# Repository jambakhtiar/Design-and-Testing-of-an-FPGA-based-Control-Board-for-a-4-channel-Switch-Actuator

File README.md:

Abstract
This project work consists of two sub-projects. On the one hand, a control board for a 4-channel
switch actuator was to be newly designed. The switch actuator has four relays that can be freely
controlled. In addition to the four buttons built into the housing, the new control board should allow
control via RS485 bus. In previous project works, this had already been carried out, but for this
work, an FPGA was to be used for the first time.
The FPGA used is a MachXO2-1200 from Lattice and is on a TinyFPGA AX2 development board.
The development board is so small that it can easily be mounted on the designed board via pin
headers.
In the second part of the work, a predefined communication protocol and all necessary
functionalities, as well as the control of the four buttons, are to be implemented on the FPGA. The
hardware description of the FPGA was done in the description language VHDL and is transferred to
the FPGA via a programmer. A MicroMatch interface should be placed on the control board for the
programmer.
Table of Contents
Statutory Declaration i
Abstract ii
Table of Contents iiiList of Figures vi
List of Tables vii
List of Abbreviations viii
1. Introduction 1
1.1. Objective of the Work 1
1.2. Procedure 1
2. Fundamentals 2
2.1. Data Exchange 2
2.2. Debouncing the Buttons 3
3. Problem Analysis 4
3.1. Communication Protocol 5
3.1.1. Message Fragments 6
3.1.2. Commands 6
3.1.3. Error Messages 7
4. Solution Concept 8
4.1. Reading Serial Data 8
4.2. Assembling Data 8
4.3. Generating CRC Checksum 9
4.4. Evaluating Commands 9
4.4.1. Executing Commands 9
4.5. Sending Message 10
4.5.1. Generating a Response 10
4.5.2. Sending Serial Data 10
4.6. Top Module 11
5. Implementation 12
5.1. The Module serial_reciever 12
5.1.1. Idle 13
5.1.2. Start 13
5.1.3. Data 14
5.1.4. Stop 14
5.2. The Module msg_separator 15
5.2.1. Reset 165.2.2. States 16
5.3. The Module crc_generator 17
5.4. The Module state_logic 17
5.4.1. Button Control 18
5.4.2. The Module msg_interpreter 19
5.5. The Module sender_modul 20
5.5.1. The Module msg_composer 21
5.5.2. The Module serial_sender 22
5.6. The Clock Generator 24
5.7. The Top Module 24
5.7.1. Startup and Idle 25
5.7.2. Receive and Check_crc 26
5.7.3. Check_addr 27
5.7.4. Check_cmd and exec_cmd 27
5.7.5. Send 28
5.7.6. Error States 28
6. Board Design 29
7. Commissioning 32
8. Evaluation 34
9. Summary and Outlook 35
Literature 36
A. Source Code 37
B. Circuit Diagram 42
List of Figures
5.1. Pin Assignments of the FPGA 25
6.1. FPGA with MAX485 29
6.2. Extended Board Design 30
6.3. Copper Layer has no contact to the outside on both sides 31
7.1. Buttons 1-4 and on the far left Reset; LEDs 1-4 in the back 32
List of Tables3.1. Division of Messages 6
3.2. Overview of which Relays are associated with which Operands 7
3.3. Overview of the Defined Error Codes 7
List of Abbreviations
ASCII: American Standard Code for Information Interchange 5
CR: Carriage Return 5
CRC: Cyclic Redundancy Check 4
FPGA: Field Programmable Gate Array 1
IDE: Integrated Development Environment 25
LED: Light Emitting Diode 1
LSB: Least Significant Bit 2
UART: Universal Asynchronous Receiver Transmitter 2
VHDL: Very High Speed Integrated Circuit Hardware Description Language 1
1. Introduction
During the Bachelor's degree program in Computer Science, a project with 150 hours of work is to
be completed. Due to previous collaboration with Prof. Dr. Rainer Werthebach, the idea arose to
reimplement an older project with different hardware. This involves an ELV switching module,
whose control board is to be replaced with a variant that is operated by an FPGA (Field
Programmable Gate Array).
1.1. Objective of the Work
The main objectives of this work are the design of a control board and the description of an FPGA
located on it, which allows control via the RS485 bus.
1.2. Procedure
Initially, there was a phase of familiarization with the VHDL (Very High-Speed Integrated Circuit
Hardware Description Language) description of the FPGA using the Lattice toolchain. This was
done through small test projects where LEDs (Light Emitting Diodes) and buttons were used.
Subsequently, the functionalities to be implemented were divided into individual modules, which
were then implemented and tested one by one.
Since hardware description, unlike usual programming, does not function sequentially, an
adjustment was necessary. The use of state machines proved beneficial in this regard. As they are
also very helpful for the conceptualization of processes, they were used more frequently.In parallel, there was a familiarization with circuit diagram and PCB design using the KiCad
software version 5.1.6. Based on previous project works, the control board was designed.
2. Fundamentals
2.1 Data Exchange
While the input and output signals of the control board take place via an RS485 interface, the
signals generated from it are subject to a UART (Universal Asynchronous Receiver Transmitter)
interface. This is an asynchronous, serial interface that is implemented without a clock signal. For
this work, a baud rate of 9600 bit/s is used. Since UART only allows simplex transmission, both a
sending and a receiving line are necessary.
The lines are continuously at a logical one until a logical zero arrives with the start bit of the
message stream. The following eight bits are the data bits of the message, starting with the LSB
(Least Significant Bit), followed by a logical one as the stop bit. Thus, data is transmitted byte by
byte.
Since custom modules are to be written in VHDL for serial transmission, it is necessary to measure
the bits correctly. If the value of a bit is measured immediately at the falling or rising edge of a
signal, reading the data is prone to errors. If the signal does not change its state quickly enough, it
could not be read reliably.
To avoid this source of error, one must wait until the middle of the bit after the edge has fallen and
only then measure. This ensures that the signal is at its desired HIGH or LOW voltage.
For the receiver module, one needs the number of clock cycles between the individual bits and must
start reading the data bits after half of this number. The number is calculated from the clock
frequency and the baud rate. The clock generator is built into the FPGA and is used with a
frequency of 2.08 MHz. This results in the following calculation:
Takte_pro_Bit=BaudrateTaktfrequenz
Takte_pro_Bit=9,6002,080,000≈216.667
Thus, the signal of a bit must be maintained for 217 cycles.
This value must also be used for sending the data to set the signals at the correct intervals to achieve
a baud rate of 9600.
2.2. Debouncing the Buttons
For the use of buttons, the interference effect of bouncing must be considered. This occurs due to
the mechanical pressing, where the contacts briefly spring back before making the final contact. As
a result, a stable signal is only present after a short time, and the state is fluctuating before that.
Depending on the function of the button, bouncing can lead to unwanted effects.
There are various ways to debounce buttons. In this case, debouncing is done in the FPGA using
VHDL. Upon detecting a signal, it is measured after 50 ms to see if the signal is still present, and
only then is the desired function executed. This time period is hardly noticeable for the user and issufficient to bridge the bouncing, as the bouncing times can reach up to 10 ms depending on the
button.
For this, the necessary number of clock cycles must also be calculated.
time cycles per msWait time=Clock cycles per ms×50
2080×50=104000
Section 3: Problem Analysis
The switch actuator is controlled by four signals originating from the control board. This results in
16 different states of the relays. To visualize this, four LEDs are located on the top side of the
casing to display the current state of each relay.
Additionally, the states should be toggleable manually using the buttons also located on the top side
of the casing.
The board should have an RS485 interface, which converts RS485 signals into serial signals and
forwards them to the FPGA. It should also have the same dimensions as the original board, a
voltage converter for power supply, a reset button, and a MicroMatch interface for the TinyFPGA
Programmer.
For serial signals, implementing read and write modules is necessary. Transmitted bytes must be
linked into a coherent message to check the message length. Subsequently, the message syntax must
be correct, and the proper CRC1 checksum must be calculated. If the addresses and the command
match, the command will be executed.
The FPGA requires the following inputs and outputs for these functionalities:
•
•
•
•
•
•
•
•
•
•
•
•
reset: Input
button0: Input
button1: Input
button2: Input
button3: Input
relay0: Output
relay1: Output
relay2: Output
relay3: Output
serial_in: Input
serial_out: Output
serial_enable: Output
3.1 Communication Protocol
Communication and control should take place serially over an RS485 bus. ASCII-coded bytes are
sent to make them readable in a terminal. An existing protocol from previous projects defines the
commands. The protocol specifications are:
• Message length: 12 bytes
• Encoding in ASCII•
•
•
•
•
•
Messages end with CR3
Baud rate: 9600
One start bit
Eight data bits, LSB first
One stop bit
No parity bit
3.1.1 Message Fragments
The message fragments are structured as follows:
Fragment
Encoding
Length Example
Receiver
Four numerical values, ASCII-coded 4 bytes 1001
Sender
Four numerical values, ASCII-coded 4 bytes 1001
Message
Operator + Operand, ASCII-coded 3 bytes s01
CRC Checksum
ASCII characters
4 bytes AB01
CR - Carriage Return ASCII character: CR (0x0D)
1 byte
Table 3.1: Structure of the messages
3.1.2 Commands
There are five different commands:
•
•
•
•
•
s: Turns the relay on
c: Turns the relay off
t: Toggles the relay
g: Queries the state of all relays
d: Performs a self-test (not yet defined)
3.1.3 Error Messages
Errors should be detected and reported back. Various error codes are defined for reporting, listed in
Table 3.3.
Error Code
Description
E01
CRC checksum incorrect
E02
Unknown error
E03
Packet length incorrect
E04
Command does not match the specified syntax
E05
Sender is not authorized to issue commands
Table 3.3: Overview of the defined error codes
Section 4: Solution Concept
Most functionalities can be divided into individual modules. In almost all cases, it has proven useful
to first design state machines. These allow sequential structures to be easily implemented in VHDL.4.1. Reading Serial Data
The work of the module for serial reception was based on a template. [2] From this, the necessary
processes were determined and also code parts for later implementation were taken.
A UART frame consists of ten bits. The first is the start bit, followed by eight data bits and finally
the stop bit. The data bits can be combined into a byte. Thus, it must first wait until a start bit is
detected. Then, the data bit is read eight times with the delay calculated in 2.1 and combined into a
byte. After the stop bit, the module signals that a new byte has been read.
4.2. Assembling Data
To process the data, the individual bytes must first be combined into the components of the message
protocol.
4.3. Generating CRC Checksum
Next, the syntax of the message must be correct, and the correct CRC1 checksum must be
calculated. If the addresses and the command match, the command is executed.
The FPGA requires the following inputs and outputs for these functionalities:
•
•
•
•
•
•
•
•
•
•
•
•
reset: input
taster0: input
taster1: input
taster2: input
taster3: input
relais0: output
relais1: output
relais2: output
relais3: output
serial_in: input
serial_out: output
serial_enable: output
4.4. Evaluating Commands
Commands are interpreted and executed based on predefined protocols and syntax.
4.5. Sending Messages
This involves generating a response and transmitting it serially.
4.6. Top Module
Combines all the submodules into a cohesive system .Section 5: Implementation
5.1 The Module serial_receiver
The serial_receiver module handles the reception of serial data. It consists of several states
that manage the reception process:
•
•
•
•
Idle: The module waits for a start bit.
Start: The start bit is detected and validated.
Data: Data bits are received.
Stop: The stop bit is validated and the complete byte is transferred.
vhdl
Copy code
entity SERIAL_RECEIVER is
port (
clk : in std_logic;
reset : in std_logic;
rx : in std_logic;
data_out : out std_logic_vector(7 downto 0);
ready : out std_logic
);
end SERIAL_RECEIVER;
5.2 The Module msg_separator
The msg_separator module is responsible for splitting incoming messages into their respective
components. This includes resetting the module, handling various states, and signaling errors.
5.2.1 Reset
The reset functionality clears all internal counters and sets the state machine back to its initial state.
vhdl
Copy code
if in_reset = '1' then
out_e3_signal <= '0';
counter_rec <= 0;
counter_snd <= 0;
counter_cmd <= 0;
counter_crc <= 0;
msg_receiver <= (others => '0');
msg_sender <= (others => '0');
msg_cmd <= (others => '0');
msg_crc <= (others => '0');
fsm_state <= receiver;
end if;
5.2.2 States
The module transitions through several states to separate the message components.
vhdl
Copy code
elsif in_signal = '1' then
case fsm_state is
when receiver =>
if in_msg = cr_ref thenfsm_state <= receiver;
counter_rec <= 0;
out_e3_signal <= '1';
else
<= in_msg;
msg_receiver(7 + (counter_rec * 8) downto 0 + (counter_rec * 8))
if counter_rec < 3 then
counter_rec <= counter_rec + 1;
else
fsm_state <= sender;
counter_rec <= 0;
end if;
end if;
when sender =>
-- Additional state logic
when cmd =>
-- Additional state logic
when crc =>
-- Additional state logic
when cr =>
if in_msg = cr_ref then
msg_cr <= in_msg;
msg_done <= '1';
fsm_state <= receiver;
else
out_e3_signal <= '1';
fsm_state <= receiver;
end if;
end case;
end if;
5.3 The Module crc_generator
The crc_generator module calculates the CRC checksum for the received message.
vhdl
Copy code
entity CRC_GENERATOR is
port (
clk : in std_logic;
in_signal : in std_logic;
in_rec : in std_logic_vector(31 downto 0);
in_sender : in std_logic_vector(31 downto 0);
in_cmd : in std_logic_vector(23 downto 0);
out_signal : out std_logic;
out_crc : out std_logic_vector(31 downto 0)
);
end CRC_GENERATOR;
5.4 The Module state_logic
The state_logic module manages state transitions and the execution of commands.
vhdl
Copy code
entity STATE_LOGIC is
port (
clk : in std_logic;
reset : in std_logic;
msg_signal : in std_logic;
button_signal : in std_logic;
in_cmd : in std_logic_vector(23 downto 0);in_button0 : in std_logic;
in_button1 : in std_logic;
in_button2 : in std_logic;
in_button3 : in std_logic;
state_out : out std_logic_vector(3 downto 0);
state_msg : out std_logic_vector(23 downto 0);
request_signal : out std_logic;
out_e2_signal : out std_logic;
out_e4_signal : out std_logic
);
end STATE_LOGIC;
5.4.1 Button Operation
When a button is pressed during the idle state, the state machine transitions to btn_proc to
process the button press.
vhdl
Copy code
when btn_proc =>
v_Count := v_Count + 1;
if v_Count = 104000 then
if button_signal = '1' then
if in_button0 = '0' then
current_state(0) <= not current_state(0);
end if;
if in_button1 = '0' then
current_state(1) <= not current_state(1);
end if;
if in_button2 = '0' then
current_state(2) <= not current_state(2);
end if;
if in_button3 = '0' then
current_state(3) <= not current_state(3);
end if;
fsm_lgc_state <= fin;
else
v_Count := 0;
fsm_lgc_state <= idle;
end if;
end if;
5.5 The Module sender_modul
The sender_modul handles the sending of messages, including composing the message and
transmitting it via serial communication.
5.5.1 The Module msg_composer
This module assembles the message to be sent.
5.5.2 The Module serial_sender
The serial_sender transmits the composed message over the serial interface.Section 6: PCB Design
During the project, the FPGA was only used in a test setup on breadboards.
Figure 6.1: FPGA with MAX485
However, a carrier board should be designed on which the tinyFPGA board can be mounted.
Additionally, a reset button and a MicroMatch port for programming the FPGA should be added.
For the design, power supply, RS485 interface, and dimensions from a previous project were
adopted. Expanding this was a task of lesser size.
Initially, the circuit diagram was designed, with some elements also taken from the previous work
(see Appendix B).
Figure 6.2: Extended PCB Design
When routing the traces, it must be ensured that they do not run at 90-degree angles, do not cross
each other, and are not too close together. The angles can usually be maintained with the automation
provided by KiCad, although manual correction is sometimes necessary. In case of space issues, it is
helpful to narrow the traces in places or move them to the other side of the board.
Section 7: Commissioning
For commissioning, the button/LED board was replicated on a breadboard with an additional reset
button. This setup allowed for testing whether the outputs were correctly switched and the buttons
were properly read at any time. This was particularly useful during the development phase for basic
debugging.
Figure 7.1: Buttons 1-4 and reset on the far left; LEDs 1-4 at the back
At the end, it was checked whether the actual board worked the same way with the FPGA. Since
wiring errors could have occurred during the reconstruction, this was a necessary step. It turned out
that the circuit diagram was correctly read and implemented.
The control via terminal was successfully tested. All commands are executed correctly, and in case
of errors, the corresponding error messages are returned. Only the generation of the CRC checksum
remains an unresolved problem. The development of the CRC module was mainly carried out using
the simulator to be able to trace the calculated values step by step. While the checksums were
correctly displayed in the simulator, they were always the same and therefore incorrect during
actual operation. It was not possible to determine what caused this problem.
Since the control board was only designed but not created at the time of the project, actual
commissioning was not yet possible.
It also turned out that the programmer, which is plugged into the tinyFPGA board, has an impact on
the MAX485 module. Therefore, the serial ports cannot be used without the programmer attached.
Since the programmer was attached the entire time during the development phase, this was only
noticed at the very end.Section 8: Evaluation
The fundamental tasks were successfully completed. Relays can be toggled with debounced buttons,
commands transmitted via RS485 are correctly processed, and executed according to the
communication protocol. Errors mentioned there are also detected and acknowledged with
corresponding messages.
A new control board was designed to accommodate the tinyFPGA board, featuring a MicroMatch
port and the necessary components for power supply and RS485 interface. The dimensions of the
original board were maintained to allow installation in the ELV switch actuator housing.
Section 9: Summary and Outlook
The description of the FPGA makes it possible to control the relays of an ELV switch actuator via
an RS485 bus. Control can also be achieved by pressing the built-in buttons. It is possible to control
multiple devices differently, provided they are connected via the same bus.
With the developed interface, these switch actuators can automate further actuators. Potential
applications include home automation.

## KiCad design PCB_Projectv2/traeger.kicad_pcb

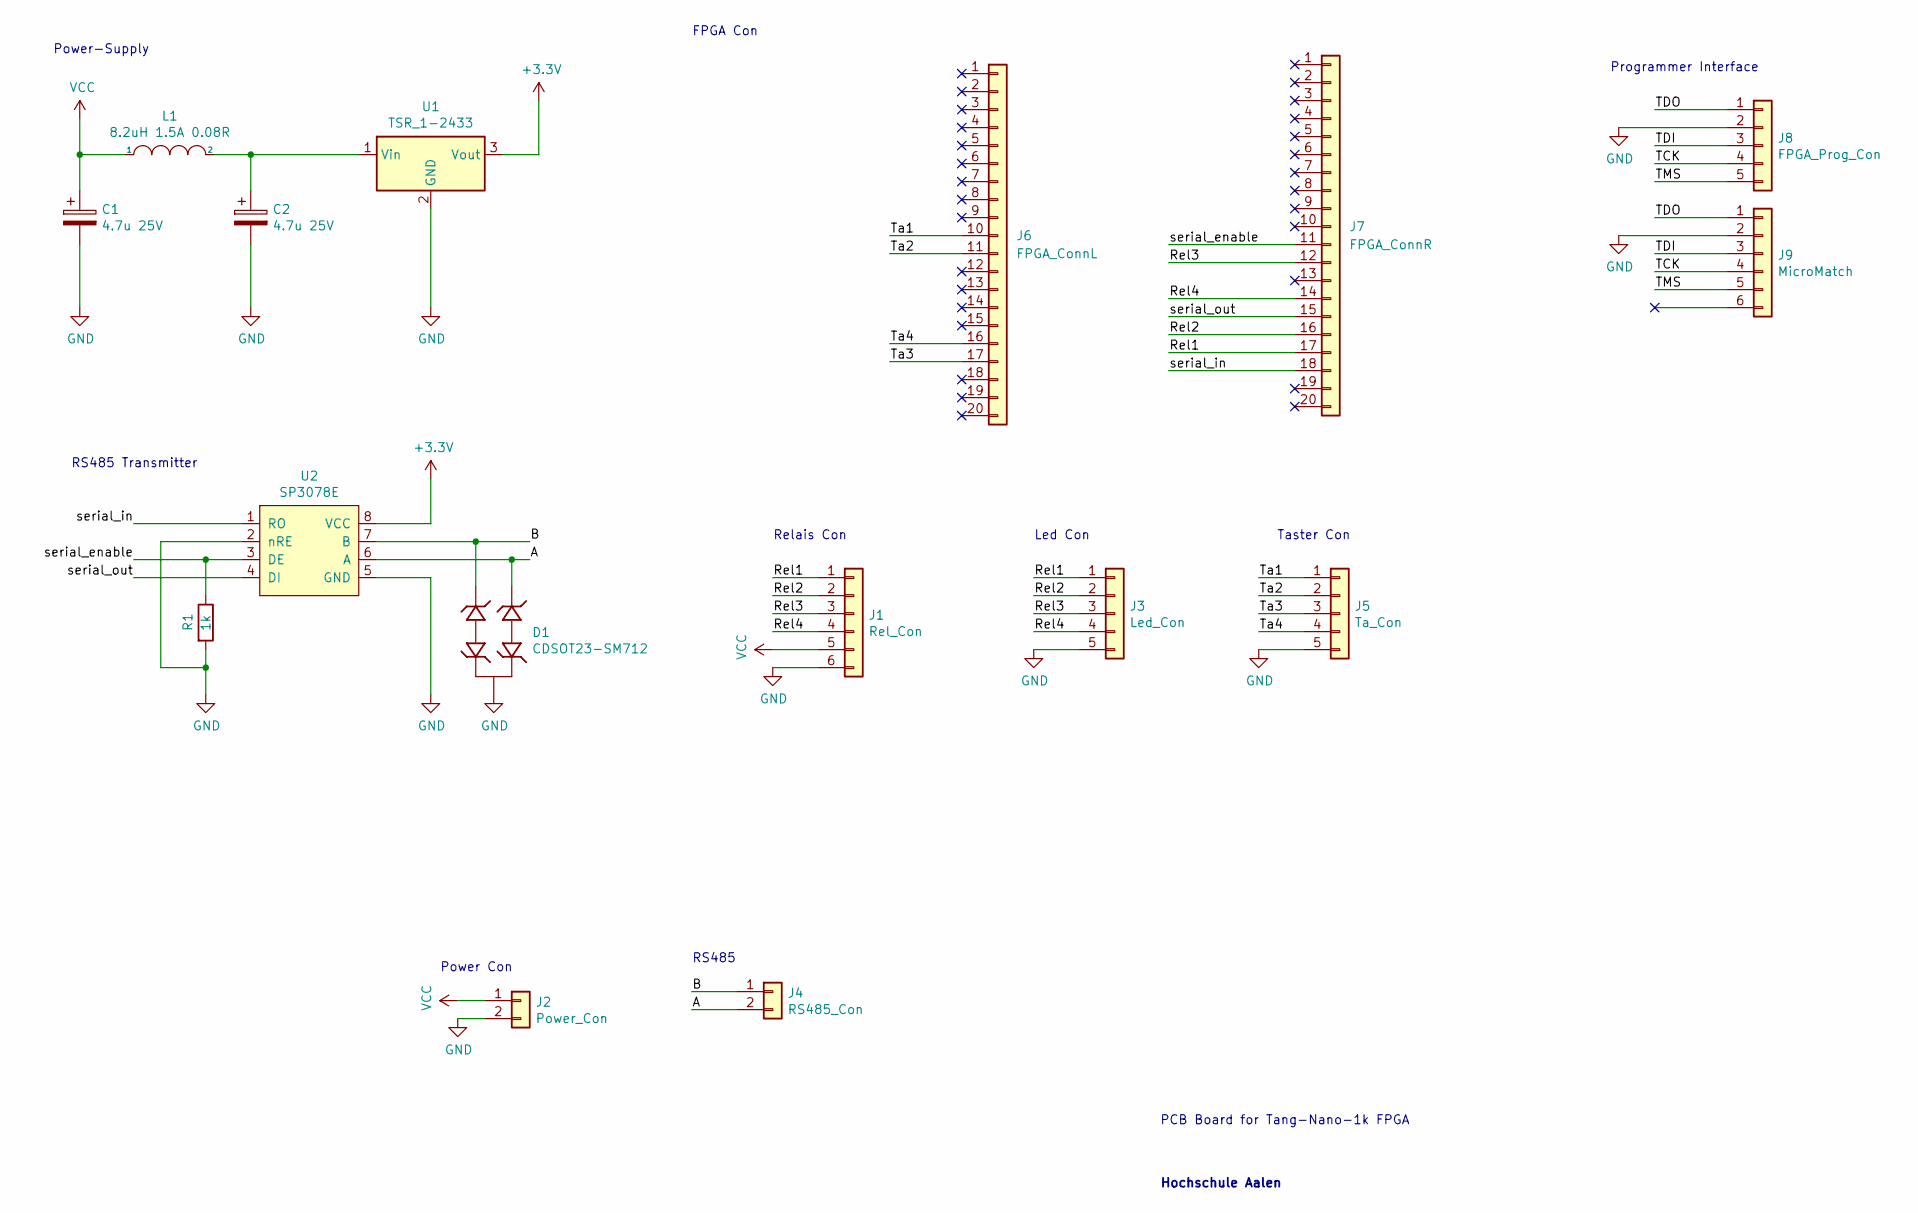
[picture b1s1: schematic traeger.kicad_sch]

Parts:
C1, C2: 4.7u 25V; CP_Elec_5x5.3
D1: CDSOT23-SM712; SOT-23-3
J1: Rel_Con; PinSocket_1x06_P2.54mm_Vertical
J2: Power_Con; TerminalBlock_bornier-2_P5.08mm
J3: Led_Con; PinSocket_1x05_P2.54mm_Vertical
J4: RS485_Con; TerminalBlock_bornier-2_P5.08mm
J5: Ta_Con; PinSocket_1x05_P2.54mm_Vertical
J6: FPGA_ConnL; PinSocket_1x20_P2.54mm_Vertical
J7: FPGA_ConnR; PinSocket_1x20_P2.54mm_Vertical
J8: FPGA_Prog_Con; PinSocket_1x05_P2.54mm_Vertical
J9: MicroMatch; micromatch_2x3pol
L1: 8.2uH 1.5A 0.08R; L_Radial_D8.7mm_P5.00mm_Fastron_07HCP
R1: 1k; R_0805_2012Metric
U1: TSR_1-2433; Converter_DCDC_TRACO_TSR-1_THT
U2: SP3078E; SOIC127P600X175-8N

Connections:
+3V3: U1.3 (Vout), U2.8 (VCC)
/A: D1.2 (IO2), J4.2, U2.6 (A)
/B: D1.1 (IO1), J4.1, U2.7 (B)
/Rel1: J1.1, J3.1, J7.17
/Rel2: J1.2, J3.2, J7.16
/Rel3: J1.3, J3.3, J7.12
/Rel4: J1.4, J3.4, J7.14
/TCK: J8.4, J9.4
/TDI: J8.3, J9.3
/TDO: J8.1, J9.1
/TMS: J8.5, J9.5
/Ta1: J5.1, J6.10
/Ta2: J5.2, J6.11
/Ta3: J5.3, J6.17
/Ta4: J5.4, J6.16
/serial_enable: J7.11, R1.1, U2.3 (DE)
/serial_in: J7.18, U2.1 (RO)
/serial_out: J7.15, U2.4 (DI)
GND: C1.2, C2.2, D1.3 (GND), J1.6, J2.2, J3.5, J5.5, J8.2, J9.2, R1.2, U1.2 (GND), U2.2 (nRE), U2.5 (GND)
unnamed: C2.1, L1.2, U1.1 (Vin)
VCC: C1.1, J1.5, J2.1, L1.1

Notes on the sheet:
Programmer Interface
Led Con
Relais Con
PCB Board for Tang-Nano-1k FPGA
Power Con
RS485
RS485 Transmitter
Hochschule Aalen
Power-Supply
FPGA Con
Taster Con

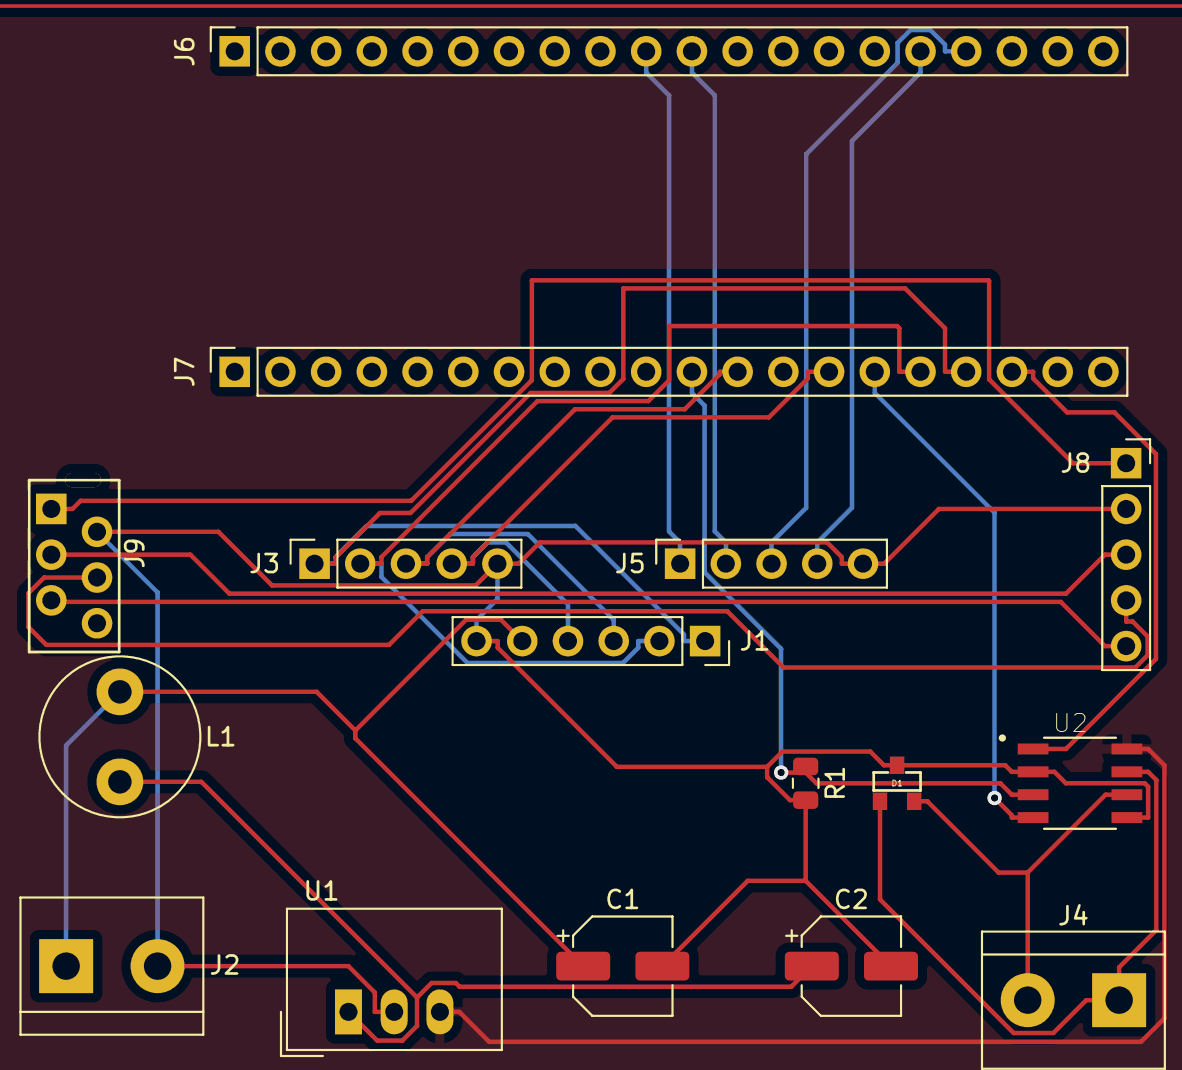
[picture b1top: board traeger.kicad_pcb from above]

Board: 2 copper layers, 16 parts (0 on the bottom side), 21 nets.
